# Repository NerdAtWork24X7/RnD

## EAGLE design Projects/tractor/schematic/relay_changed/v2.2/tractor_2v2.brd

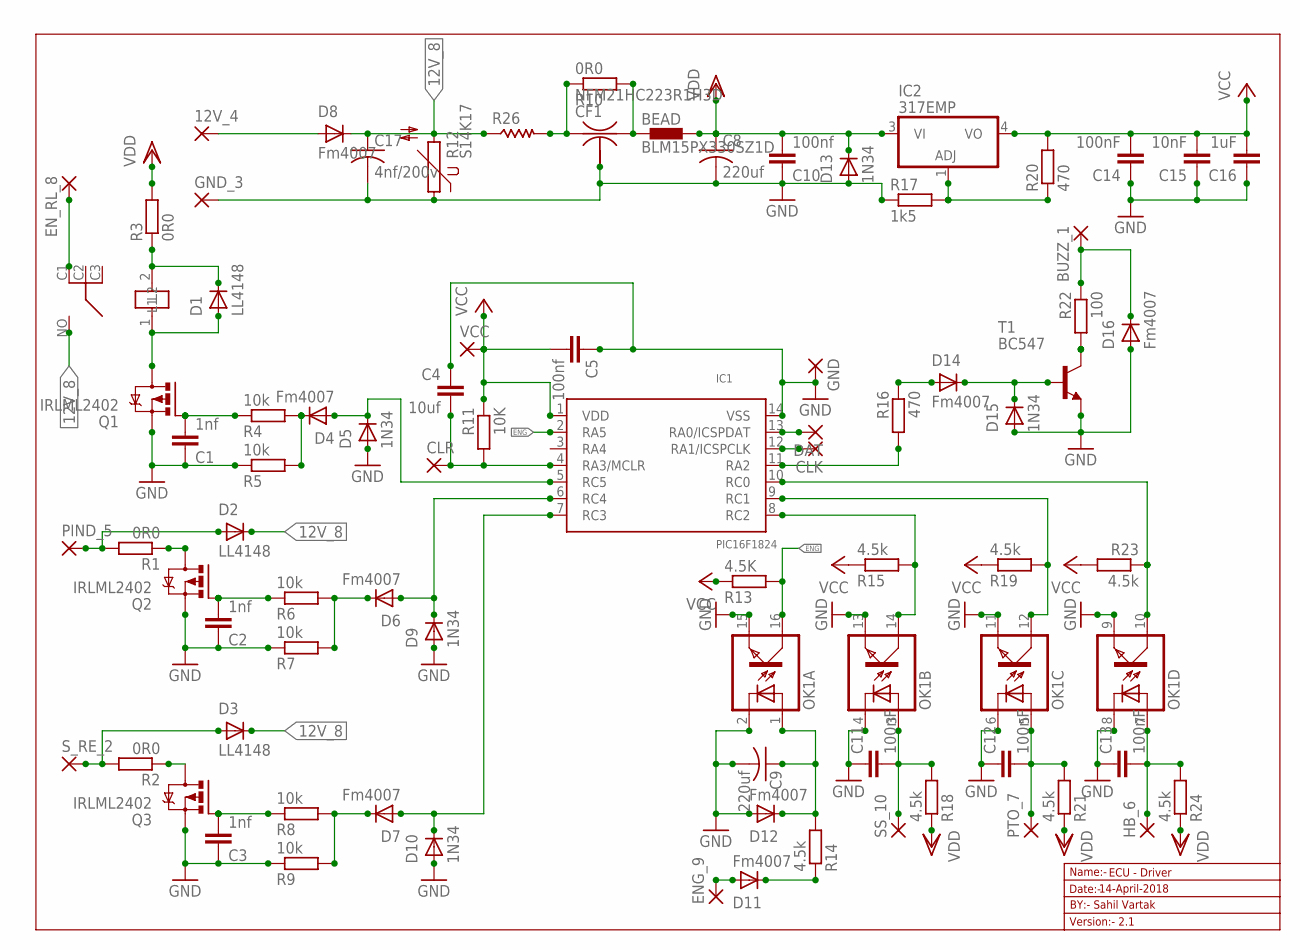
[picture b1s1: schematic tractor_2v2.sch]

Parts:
12V_4: 2,54/1,1
BEAD: BLM15PX330SZ1D; 0402
BUZZ_1: 2,54/1,1
C1, C2, C3: 1nf; C0603
C4: 10uf; C0603
C5, C10: 100nf; C0603
C8, C9: 220uf; C025-025X050
C11, C12, C13, C14: 100nF; C0603
C15: 10nF; C0603
C16: 1uF; C0603
C17: 4nf/200v; C050-045X075
CF1: NFM21HC223R1H3D; NFM3DC
CLK: 1,6/0,8
CLR: 1,6/0,8
D1, D2, D3: LL4148; SMA-DO214AC
D4, D6, D7, D8, D11, D12, D14, D16: Fm4007; SMA-DO214AC
D5, D9, D10, D13, D15: 1N34; SMA-DO214AC
DAT: 1,6/0,8
ENG_9: 2,54/1,1
EN_RL_8: 2,54/1,1
GND: 1,6/0,8
GND_3: 2,54/1,1
HB_6: 2,54/1,1
IC1: PIC16F1824; SO-14
IC2: 317EMP; SOT223
K1: RL703
OK1: TLP283-4; MINI-FLAT-16
PIND_5: 2,54/1,1
PTO_7: 2,54/1,1
Q1, Q2, Q3: IRLML2402; MICRO3
R1, R2, R3, R10: 0R0; R0603
R4, R5, R6, R7, R8, R9: 10k; R0603
R11: 10K; R0603
R12: S14K17
R13: 4.5K; R0603
R14, R15, R18, R19, R21, R23, R24: 4.5k; R0603
R16, R20: 470; R0603
R17: 1k5; R0603
R22: 100; R0603
R26: R-US_WSC2515; WSC2515
SS_10: 2,54/1,1
S_RE_2: 2,54/1,1
T1: BC547; TO92
VCC: 1,6/0,8

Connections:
12V_8: C17.1, D2.K (C), D3.K (C), D8.K (C), K1.NO, R12.2, R26.1
BUZZ_4: BUZZ_1.1, D16.K (C), R22.1
ENG: IC1.2 (RA5), OK1.16 (COL), R13.2
GND: C1.1, C2.1, C3.1, C4.1, C5.1, C8.2, C9.2, C10.1, C11.1, C12.1, C13.1, C14.1, C15.1, C16.1, C17.2, CF1.2@1 (2), D5.A, D9.A, D10.A, D12.A, D13.A, D15.A, D16.A, GND.1, GND_3.1, IC1.14 (VSS), OK1.2 (C), OK1.4 (C), OK1.6 (C), OK1.8 (C), OK1.9 (EMIT), OK1.11 (EMIT), OK1.13 (EMIT), OK1.15 (EMIT), Q1.2 (S), Q2.2 (S), Q3.2 (S), R5.1, R7.1, R9.1, R12.1, R17.1, T1.1 (E)
unnamed: D11.K (C), R14.1
unnamed: IC1.10 (RC0), OK1.10 (COL), R23.1
unnamed: D1.A, K1.1 (L2), Q1.3 (D)
unnamed: C2.2, Q2.1 (G), R6.1
unnamed: CF1.1, R10.1, R26.2
unnamed: DAT.1, IC1.13 (RA0/ICSPDAT)
unnamed: CLK.1, IC1.12 (RA1/ICSPCLK)
unnamed: D1.K (C), K1.2 (L1), R3.1
unnamed: IC2.1 (ADJ), R17.2, R20.1
unnamed: BEAD.1, CF1.3, R10.2
unnamed: D14.A, R16.1
unnamed: D4.A, D5.K (C), IC1.5 (RC5)
unnamed: C3.2, Q3.1 (G), R8.1
unnamed: D7.K (C), R8.2, R9.2
unnamed: IC1.11 (RA2), R16.2
unnamed: Q3.3 (D), R2.1
unnamed: D11.A, ENG_9.1
unnamed: C9.1, D12.K (C), OK1.1 (A), R14.2
unnamed: D6.K (C), R6.2, R7.2
unnamed: D2.A, PIND_5.1, R1.2
unnamed: D6.A, D9.K (C), IC1.6 (RC4)
unnamed: D3.A, R2.2, S_RE_2.1
unnamed: Q2.3 (D), R1.1
unnamed: 12V_4.1, D8.A
unnamed: D7.A, D10.K (C), IC1.7 (RC3)
unnamed: C1.2, Q1.1 (G), R4.1
unnamed: D4.K (C), R4.2, R5.2
unnamed: C11.2, OK1.3 (A), R18.2, SS_10.1
unnamed: C12.2, OK1.5 (A), PTO_7.1, R21.2
unnamed: C13.2, HB_6.1, OK1.7 (A), R24.2
unnamed: IC1.9 (RC1), OK1.12 (COL), R19.2
unnamed: IC1.8 (RC2), OK1.14 (COL), R15.2
unnamed: C4.2, CLR.1, IC1.4 (RA3/MCLR), R11.2
unnamed: D14.K (C), D15.K (C), T1.2 (B)
unnamed: R22.2, T1.3 (C)
R_3: EN_RL_8.1, K1.C1
VCC: C5.2, C14.2, C15.2, C16.2, IC1.1 (VDD), IC2.4 (VO), R11.1, R13.1, R15.1, R19.1, R20.2, R23.2, VCC.1
VDD: BEAD.2, C8.1, C10.2, D13.K (C), IC2.3 (VI), R3.2, R18.1, R21.1, R24.1

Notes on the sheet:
Name:-
Version:- 2.1
Date:-
ECU - Driver
BY:- Sahil Vartak
14-April-2018

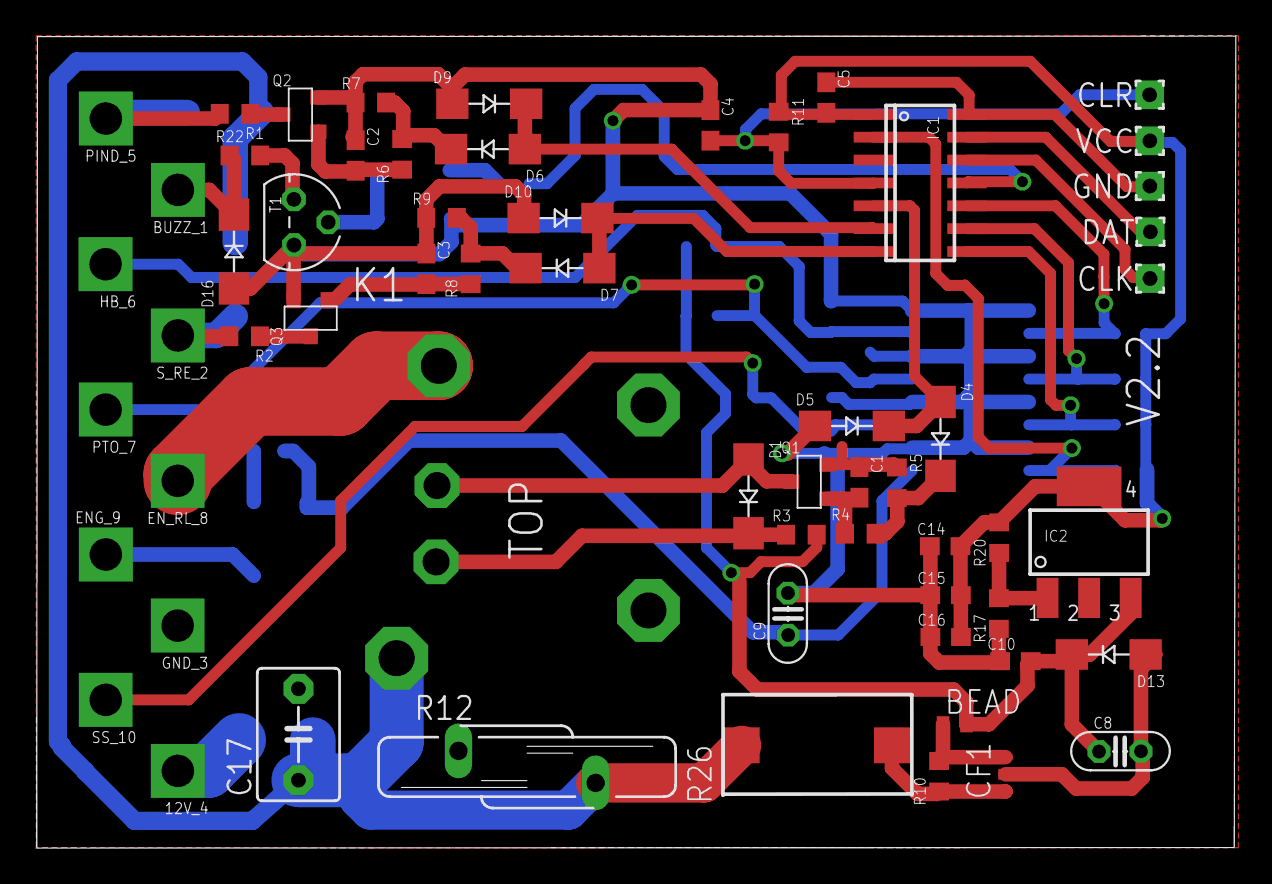
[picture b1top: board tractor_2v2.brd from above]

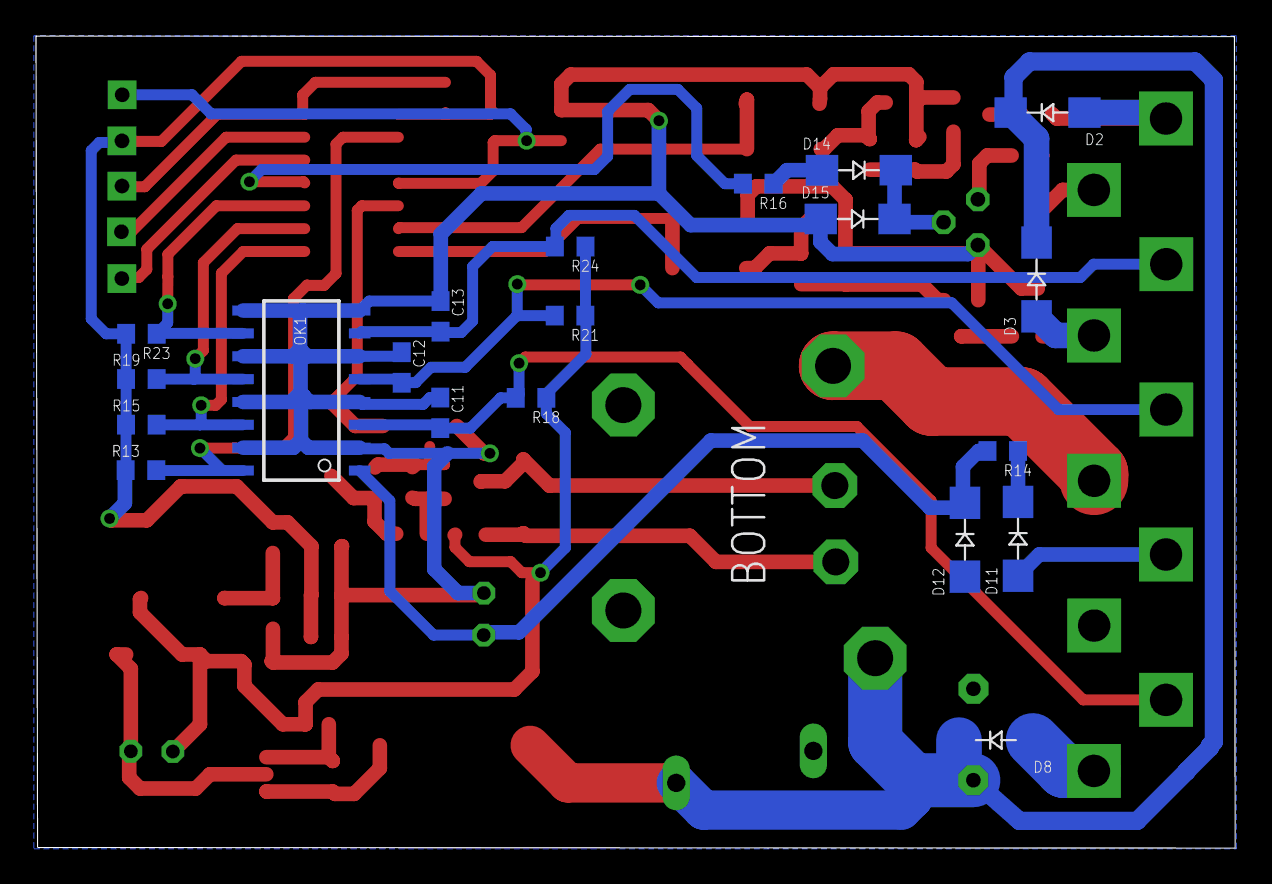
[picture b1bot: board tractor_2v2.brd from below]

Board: 2 copper layers, 66.7 x 45.1 mm, 81 parts (21 on the bottom side), 42 nets.

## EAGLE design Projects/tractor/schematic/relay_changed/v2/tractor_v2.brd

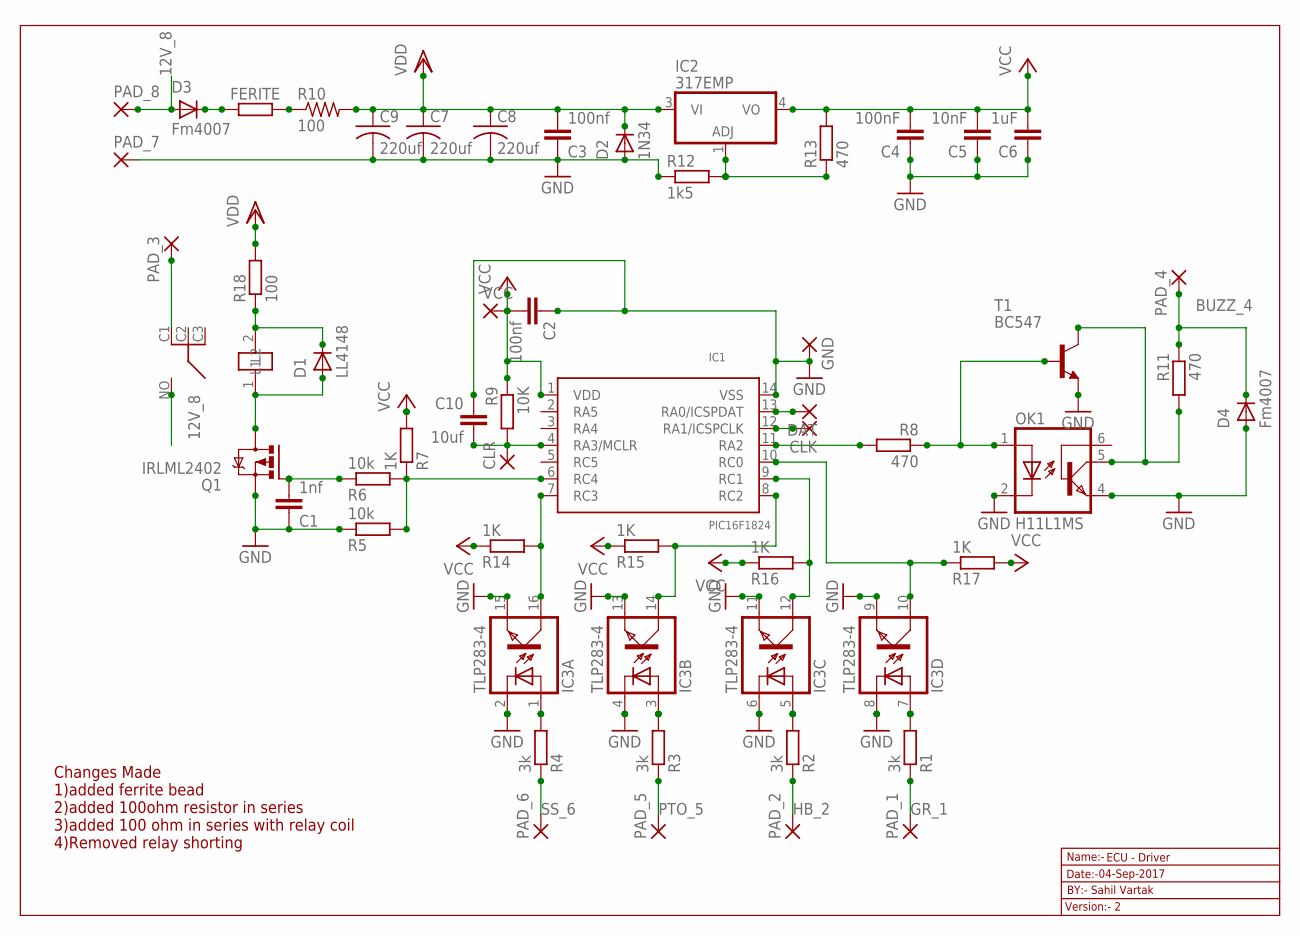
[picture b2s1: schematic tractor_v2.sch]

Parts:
C1: 1nf; C0603
C2, C3: 100nf; C0603
C4: 100nF; C0603
C5: 10nF; C0603
C6: 1uF; C0603
C7, C8, C9: 220uf; C025-025X050
C10: 10uf; C0603
CLK: 1,6/0,8
CLR: 1,6/0,8
D1: LL4148; SMA-DO214AC
D2: 1N34; SMA-DO214AC
D3, D4: Fm4007; SMA-DO214AC
DAT: 1,6/0,8
FERITE: R-EU_R0603; R0603
GND: 1,6/0,8
IC1: PIC16F1824; SO-14
IC2: 317EMP; SOT223
IC3: TLP283-4; MINI-FLAT-16
K2: RL703
OK1: H11L1MS; DIL6-SMD
PAD_1, PAD_2, PAD_3, PAD_4, PAD_5, PAD_6, PAD_7, PAD_8: 2,54/1,1
Q1: IRLML2402; MICRO3
R1, R2, R3, R4: 3k; R0603
R5, R6: 10k; R0603
R7, R14, R15, R16, R17: 1K; R0603
R8, R11, R13: 470; R0603
R9: 10K; R0603
R10: 100; WSC2515
R12: 1k5; R0603
R18: 100; R0603
T1: BC547; TO92
VCC: 1,6/0,8

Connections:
12V_8: D3.A, K2.NO, PAD_8.1
BUZZ_4: D4.K (C), PAD_4.1, R11.1
GND: C1.1, C2.1, C3.1, C4.1, C5.1, C6.1, C7.2, C8.2, C9.2, C10.1, D2.A, D4.A, GND.1, IC1.14 (VSS), IC3.2 (C), IC3.4 (C), IC3.6 (C), IC3.8 (C), IC3.9 (EMIT), IC3.11 (EMIT), IC3.13 (EMIT), IC3.15 (EMIT), OK1.2 (C), OK1.4 (EMI), PAD_7.1, Q1.2 (S), R5.1, R12.1, T1.1 (E)
GR_1: PAD_1.1, R1.1
HB_2: PAD_2.1, R2.1
unnamed: IC1.10 (RC0), IC3.10 (COL), R17.1
unnamed: D1.A, K2.1 (L2), Q1.3 (D)
unnamed: D3.K (C), FERITE.1
unnamed: DAT.1, IC1.13 (RA0/ICSPDAT)
unnamed: CLK.1, IC1.12 (RA1/ICSPCLK)
unnamed: D1.K (C), K2.2 (L1), R18.1
unnamed: IC2.1 (ADJ), R12.2, R13.1
unnamed: FERITE.2, R10.1
unnamed: C1.2, Q1.1 (G), R6.1
unnamed: IC1.6 (RC4), R5.2, R6.2, R7.1
unnamed: IC3.1 (A), R4.2
unnamed: IC3.3 (A), R3.2
unnamed: IC3.5 (A), R2.2
unnamed: IC3.7 (A), R1.2
unnamed: IC1.9 (RC1), IC3.12 (COL), R16.2
unnamed: IC1.8 (RC2), IC3.14 (COL), R15.2
unnamed: IC1.7 (RC3), IC3.16 (COL), R14.2
unnamed: C10.2, CLR.1, IC1.4 (RA3/MCLR), R9.2
unnamed: IC1.11 (RA2), R8.2
unnamed: OK1.1 (A), R8.1, T1.2 (B)
unnamed: OK1.5 (COL), R11.2, T1.3 (C)
PTO_5: PAD_5.1, R3.1
R_3: K2.C1, PAD_3.1
SS_6: PAD_6.1, R4.1
VCC: C2.2, C4.2, C5.2, C6.2, IC1.1 (VDD), IC2.4 (VO), R7.2, R9.1, R13.2, R14.1, R15.1, R16.1, R17.2, VCC.1
VDD: C3.2, C7.1, C8.1, C9.1, D2.K (C), IC2.3 (VI), R10.2, R18.2

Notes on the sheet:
Name:-
Version:- 2
Date:-
ECU - Driver
BY:- Sahil Vartak
04-Sep-2017
Changes Made 1)added ferrite bead 2)added 100ohm resistor in series 3)added 100 ohm in series with relay coil 4)Removed relay shorting

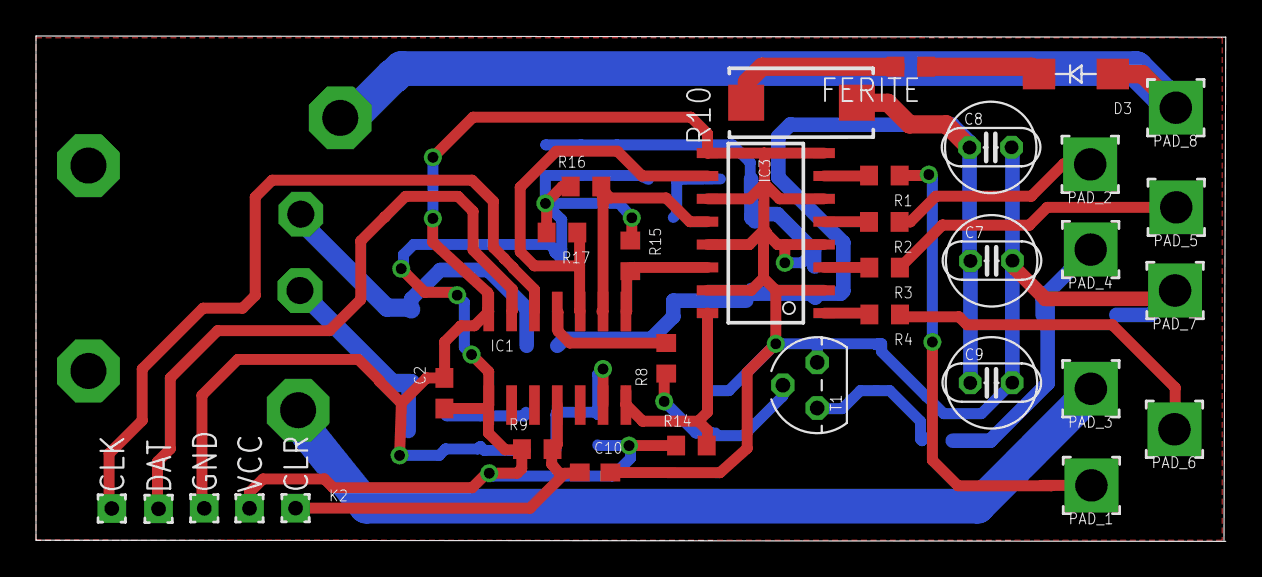
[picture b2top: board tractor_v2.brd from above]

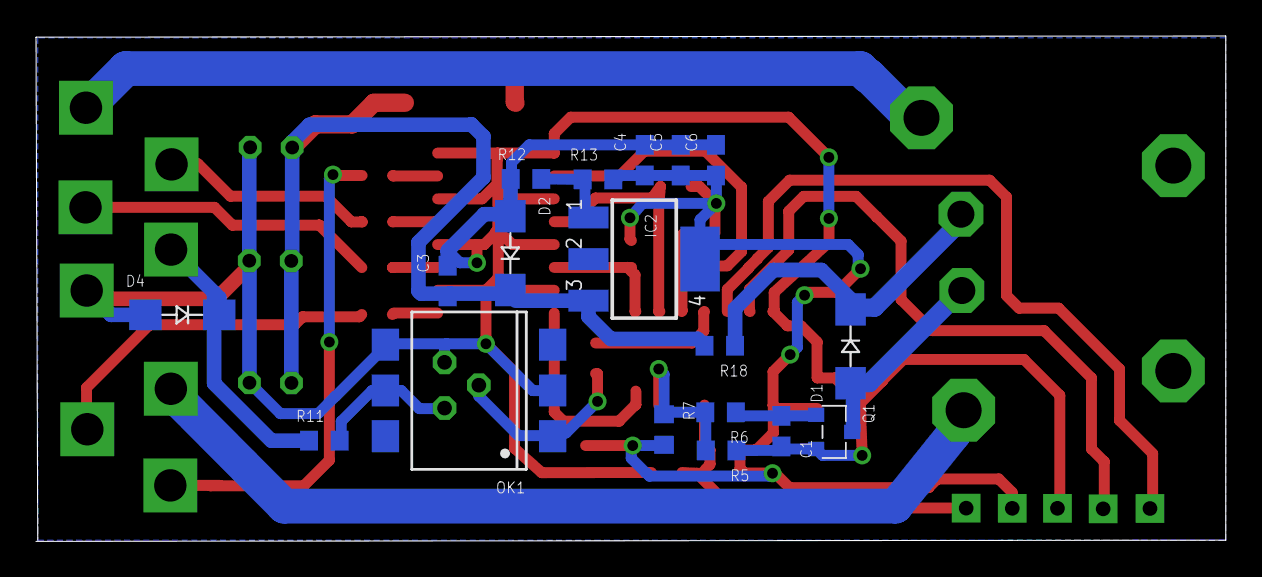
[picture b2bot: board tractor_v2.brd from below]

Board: 2 copper layers, 66.1 x 28.1 mm, 53 parts (19 on the bottom side), 31 nets.

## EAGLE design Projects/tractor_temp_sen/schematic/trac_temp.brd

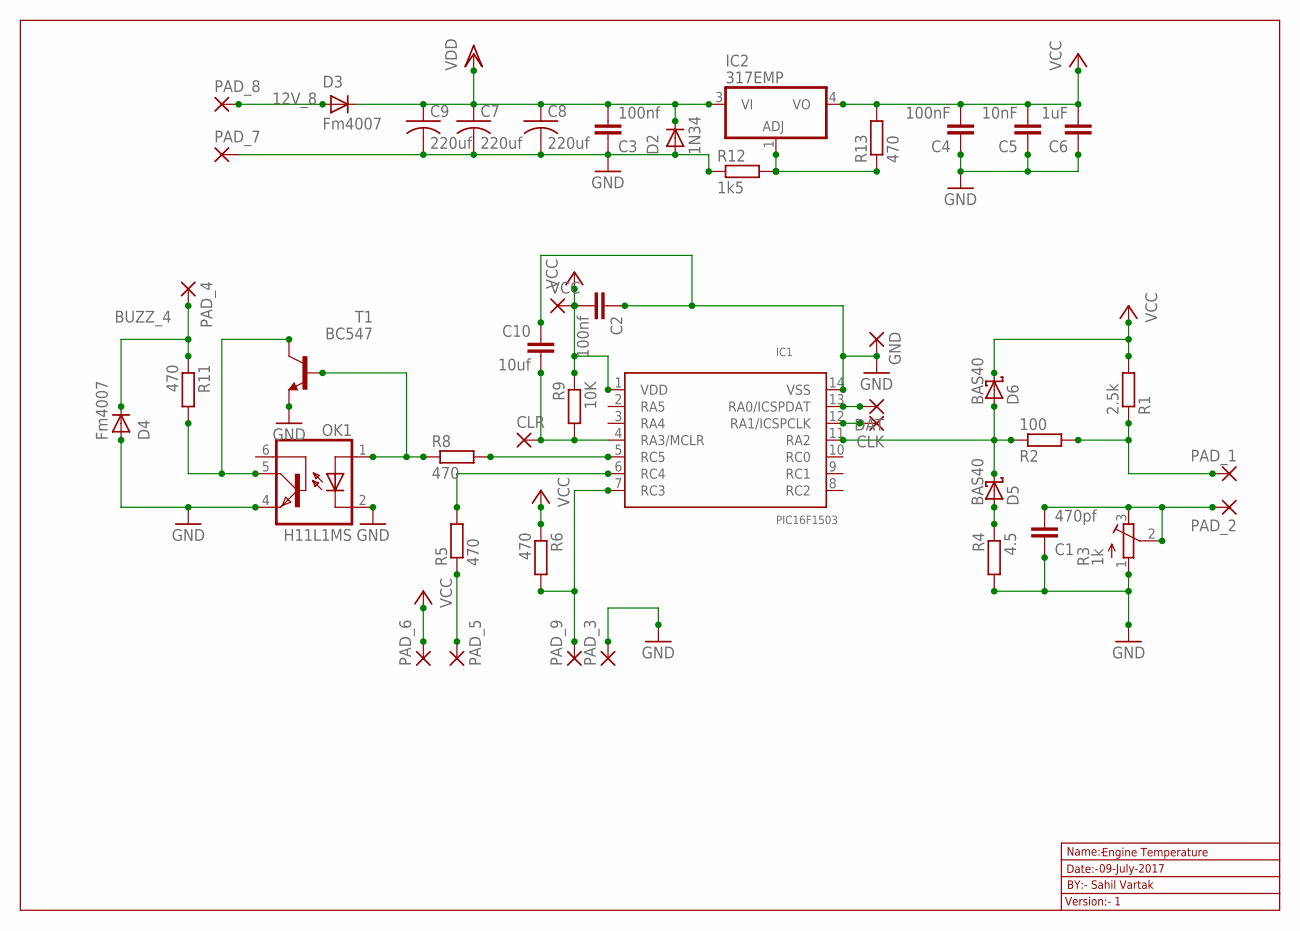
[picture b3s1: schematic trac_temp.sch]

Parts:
C1: 470pf; C0603
C2, C3: 100nf; C0603
C4: 100nF; C0603
C5: 10nF; C0603
C6: 1uF; C0603
C7, C8, C9: 220uf; C025-025X050
C10: 10uf; C0603
CLK: 1,6/0,8
CLR: 1,6/0,8
D2: 1N34; SMA-DO214AC
D3, D4: Fm4007; SMA-DO214AC
D5, D6: BAS40; SOT23
DAT: 1,6/0,8
GND: 1,6/0,8
IC1: PIC16F1503; SO-14
IC2: 317EMP; SOT223
OK1: H11L1MS; DIL6-SMD
PAD_1, PAD_2, PAD_3, PAD_4, PAD_5, PAD_6, PAD_7, PAD_8, PAD_9: 2,54/1,1
R1: 2.5k; R0603
R2: 100; R0603
R3: 1k; RTRIM3103
R4: 4.5; R0603
R5, R6, R8, R11, R13: 470; R0603
R9: 10K; R0603
R12: 1k5; R0603
T1: BC547; TO92
VCC: 1,6/0,8

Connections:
12V_8: D3.A, PAD_8.1
BUZZ_4: D4.K (C), PAD_4.1, R11.1
GND: C1.1, C2.1, C3.1, C4.1, C5.1, C6.1, C7.2, C8.2, C9.2, C10.1, D2.A, D4.A, GND.1, IC1.14 (VSS), OK1.2 (C), OK1.4 (EMI), PAD_3.1, PAD_7.1, R3.1 (A), R4.2, R12.1, T1.1 (E)
unnamed: PAD_1.1, R1.1, R2.2
unnamed: D5.1 (A), R4.1
unnamed: C1.2, PAD_2.1, R3.2 (S), R3.3 (E)
unnamed: DAT.1, IC1.13 (RA0/ICSPDAT)
unnamed: CLK.1, IC1.12 (RA1/ICSPCLK)
unnamed: C10.2, CLR.1, IC1.4 (RA3/MCLR), R9.2
unnamed: IC2.1 (ADJ), R12.2, R13.1
unnamed: D5.3 (C), D6.1 (A), IC1.11 (RA2), R2.1
unnamed: IC1.5 (RC5), R8.2
unnamed: PAD_5.1, R5.1
unnamed: IC1.6 (RC4), R5.2
unnamed: IC1.7 (RC3), PAD_9.1, R6.2
unnamed: OK1.1 (A), R8.1, T1.2 (B)
unnamed: OK1.5 (COL), R11.2, T1.3 (C)
VCC: C2.2, C4.2, C5.2, C6.2, D6.3 (C), IC1.1 (VDD), IC2.4 (VO), PAD_6.1, R1.2, R6.1, R9.1, R13.2, VCC.1
VDD: C3.2, C7.1, C8.1, C9.1, D2.K (C), D3.K (C), IC2.3 (VI)

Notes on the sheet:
Name:-
Version:- 1
Date:-
Engine Temperature
BY:- Sahil Vartak
09-July-2017

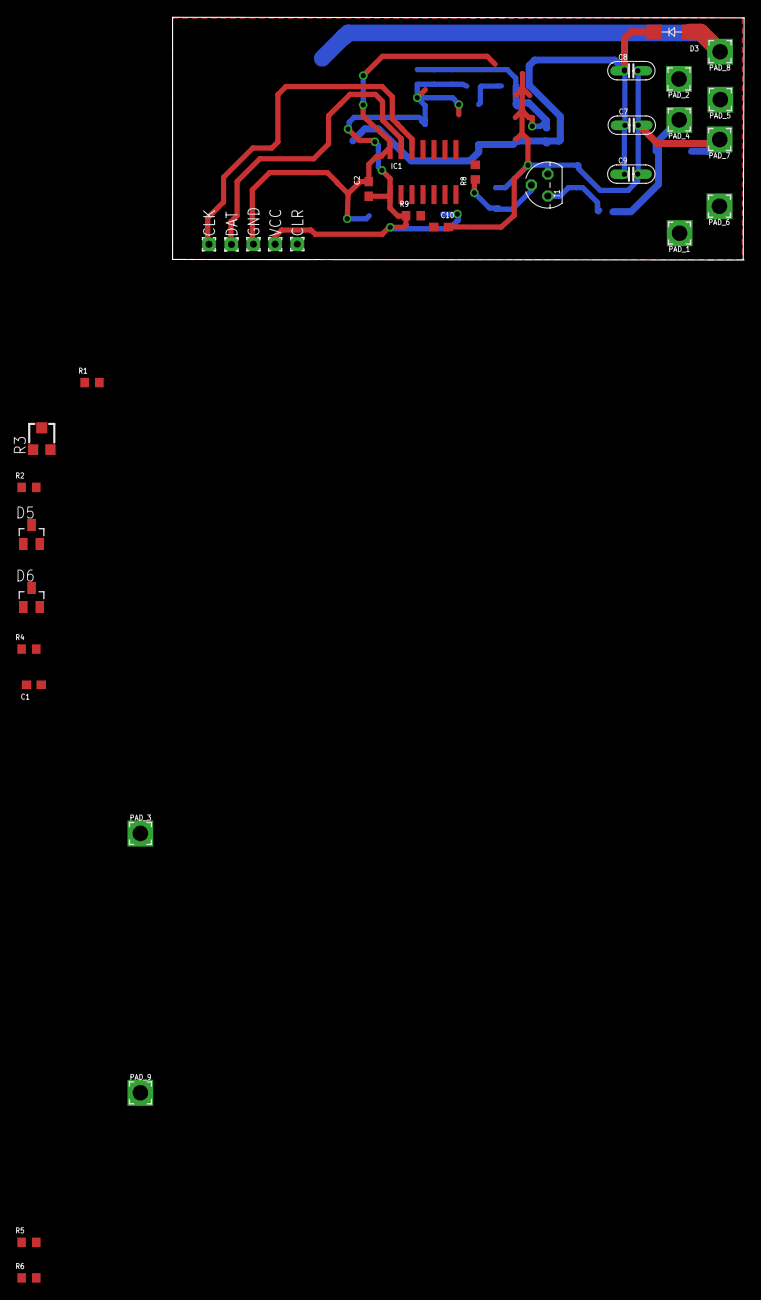
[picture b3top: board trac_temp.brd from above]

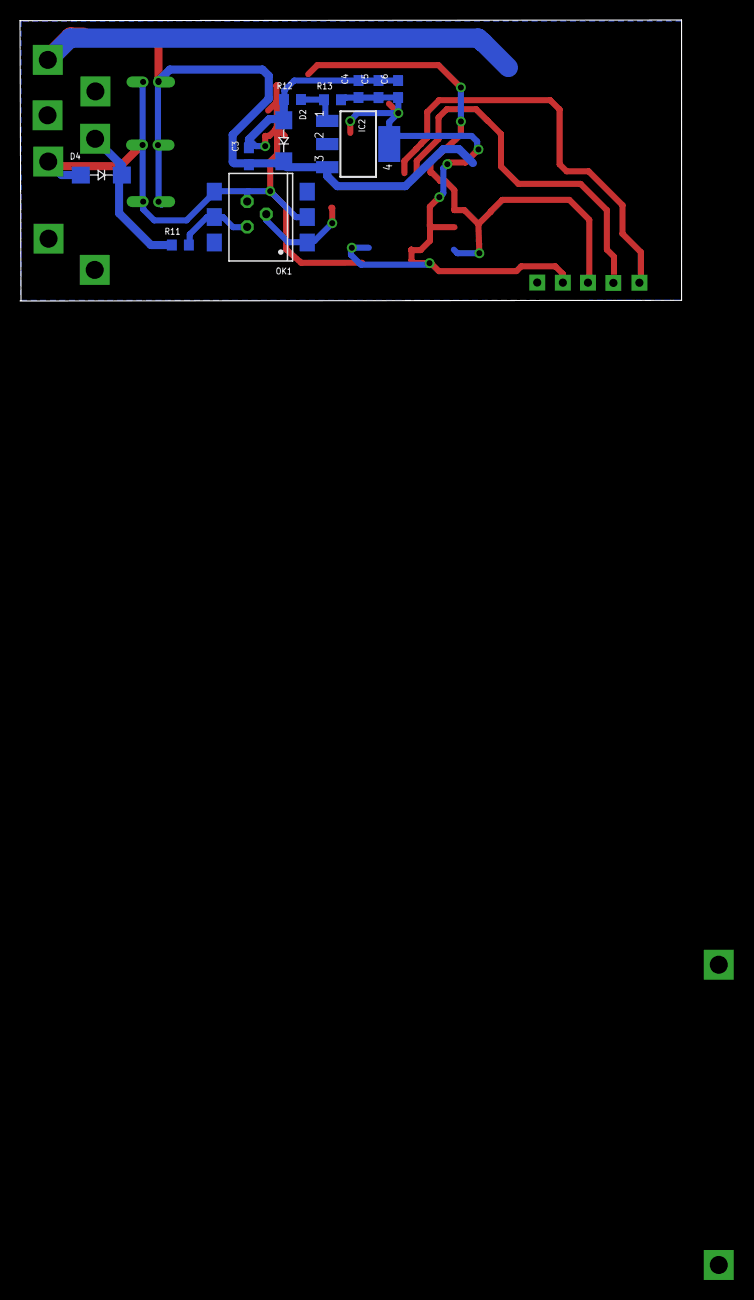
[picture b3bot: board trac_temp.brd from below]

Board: 2 copper layers, 66.1 x 28.1 mm, 44 parts (11 on the bottom side), 19 nets.
